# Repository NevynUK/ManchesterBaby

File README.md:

# ManchesterBaby
Manchester Baby (Small Scale Experimental Machine)

The [Manchester Small Scale Experimental Machine](https://en.wikipedia.org/wiki/Manchester_Small-Scale_Experimental_Machine) was the worlds first computer capable of executing a stored program.  The 32-bit architecture utilised an instruction set using only 3 bits allowing 8 possible instructions.  The program was stored in 32 memory locations (or store lines) with both data and program sharing storage (von Neumann architecture).

## Emulator

The Emulator implements a simplified version of the Manchester Baby.  The main program is able to read simple assembler files and execute the programs contained.  The program displays the status of the machine at the start and end of the program run.

Source files for the emulator are available for the following platforms:

* C++ Desktop
* C++ Running on NuttX RTOS (Coming Soon)
* Python Desktop

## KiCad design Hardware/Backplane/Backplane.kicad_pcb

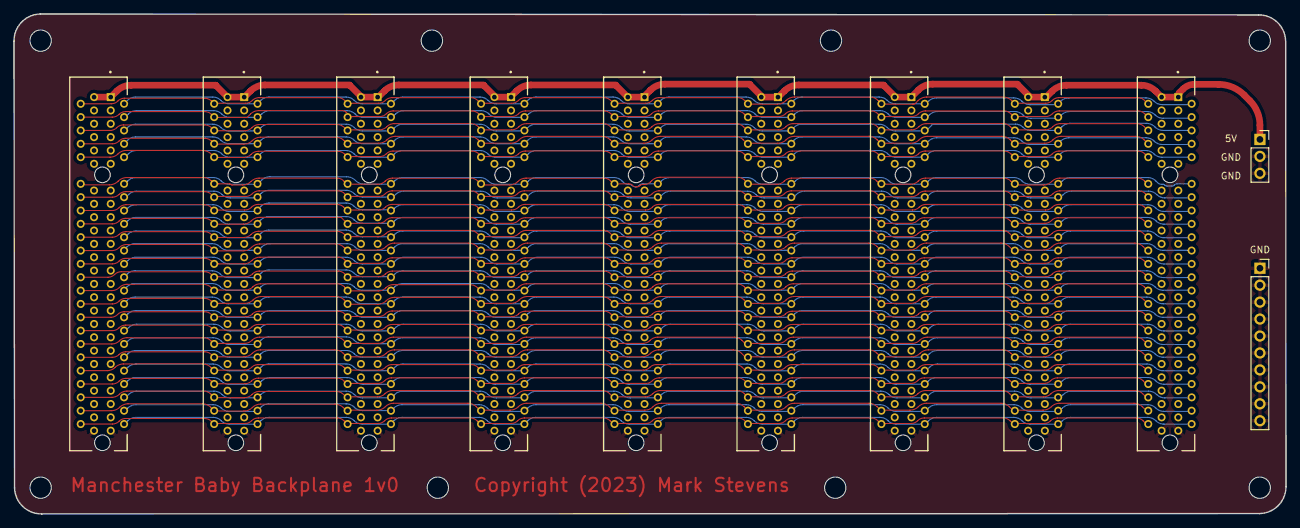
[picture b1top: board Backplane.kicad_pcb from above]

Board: 4 copper layers, 190.6 x 74.9 mm, 19 parts (0 on the bottom side), 96 nets.

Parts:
GND: Conn_01x10; PinSocket_1x10_P2.54mm_Vertical
H1, H2, H3, H4, H5, H6, H7, H8: MountingHole; MountingHole_3.2mm_M3
J1, J2, J3, J5, J6, J7, J8, J9, J10: PCIE-098-02-X-D-TH; SAMTEC_PCIE-098-02-X-D-TH
Power: Conn_01x03; PinSocket_1x03_P2.54mm_Vertical

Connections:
/A2: J1.A2, J2.A2, J3.A2, J5.A2, J6.A2, J7.A2, J8.A2, J9.A2, J10.A2
/A3: J1.A3, J2.A3, J3.A3, J5.A3, J6.A3, J7.A3, J8.A3, J9.A3, J10.A3
/A4: J1.A4, J2.A4, J3.A4, J5.A4, J6.A4, J7.A4, J8.A4, J9.A4, J10.A4
/A5: J1.A5, J2.A5, J3.A5, J5.A5, J6.A5, J7.A5, J8.A5, J9.A5, J10.A5
/A6: J1.A6, J2.A6, J3.A6, J5.A6, J6.A6, J7.A6, J8.A6, J9.A6, J10.A6
/A7: J1.A7, J2.A7, J3.A7, J5.A7, J6.A7, J7.A7, J8.A7, J9.A7, J10.A7
/A8: J1.A8, J2.A8, J3.A8, J5.A8, J6.A8, J7.A8, J8.A8, J9.A8, J10.A8
/A9: J1.A9, J2.A9, J3.A9, J5.A9, J6.A9, J7.A9, J8.A9, J9.A9, J10.A9
/A10: J1.A10, J2.A10, J3.A10, J5.A10, J6.A10, J7.A10, J8.A10, J9.A10, J10.A10
/A11: J1.A11, J2.A11, J3.A11, J5.A11, J6.A11, J7.A11, J8.A11, J9.A11, J10.A11
/A12: J1.A12, J2.A12, J3.A12, J5.A12, J6.A12, J7.A12, J8.A12, J9.A12, J10.A12
/A13: J1.A13, J2.A13, J3.A13, J5.A13, J6.A13, J7.A13, J8.A13, J9.A13, J10.A13
/A14: J1.A14, J2.A14, J3.A14, J5.A14, J6.A14, J7.A14, J8.A14, J9.A14, J10.A14
/A15: J1.A15, J2.A15, J3.A15, J5.A15, J6.A15, J7.A15, J8.A15, J9.A15, J10.A15
/A16: J1.A16, J2.A16, J3.A16, J5.A16, J6.A16, J7.A16, J8.A16, J9.A16, J10.A16
/A17: J1.A17, J2.A17, J3.A17, J5.A17, J6.A17, J7.A17, J8.A17, J9.A17, J10.A17
/A18: J1.A18, J2.A18, J3.A18, J5.A18, J6.A18, J7.A18, J8.A18, J9.A18, J10.A18
/A19: J1.A19, J2.A19, J3.A19, J5.A19, J6.A19, J7.A19, J8.A19, J9.A19, J10.A19
/A20: J1.A20, J2.A20, J3.A20, J5.A20, J6.A20, J7.A20, J8.A20, J9.A20, J10.A20
/A21: J1.A21, J2.A21, J3.A21, J5.A21, J6.A21, J7.A21, J8.A21, J9.A21, J10.A21
/A22: J1.A22, J2.A22, J3.A22, J5.A22, J6.A22, J7.A22, J8.A22, J9.A22, J10.A22
/A23: J1.A23, J2.A23, J3.A23, J5.A23, J6.A23, J7.A23, J8.A23, J9.A23, J10.A23
/A24: J1.A24, J2.A24, J3.A24, J5.A24, J6.A24, J7.A24, J8.A24, J9.A24, J10.A24
/A25: J1.A25, J2.A25, J3.A25, J5.A25, J6.A25, J7.A25, J8.A25, J9.A25, J10.A25
/A26: J1.A26, J2.A26, J3.A26, J5.A26, J6.A26, J7.A26, J8.A26, J9.A26, J10.A26
/A27: J1.A27, J2.A27, J3.A27, J5.A27, J6.A27, J7.A27, J8.A27, J9.A27, J10.A27
/A28: J1.A28, J2.A28, J3.A28, J5.A28, J6.A28, J7.A28, J8.A28, J9.A28, J10.A28
/A29: J1.A29, J2.A29, J3.A29, J5.A29, J6.A29, J7.A29, J8.A29, J9.A29, J10.A29
/A30: J1.A30, J2.A30, J3.A30, J5.A30, J6.A30, J7.A30, J8.A30, J9.A30, J10.A30
/A31: J1.A31, J2.A31, J3.A31, J5.A31, J6.A31, J7.A31, J8.A31, J9.A31, J10.A31
/A32: J1.A32, J2.A32, J3.A32, J5.A32, J6.A32, J7.A32, J8.A32, J9.A32, J10.A32
/A33: J1.A33, J2.A33, J3.A33, J5.A33, J6.A33, J7.A33, J8.A33, J9.A33, J10.A33
/A34: J1.A34, J2.A34, J3.A34, J5.A34, J6.A34, J7.A34, J8.A34, J9.A34, J10.A34
/A35: J1.A35, J2.A35, J3.A35, J5.A35, J6.A35, J7.A35, J8.A35, J9.A35, J10.A35
/A36: J1.A36, J2.A36, J3.A36, J5.A36, J6.A36, J7.A36, J8.A36, J9.A36, J10.A36
/A37: J1.A37, J2.A37, J3.A37, J5.A37, J6.A37, J7.A37, J8.A37, J9.A37, J10.A37
/A38: J1.A38, J2.A38, J3.A38, J5.A38, J6.A38, J7.A38, J8.A38, J9.A38, J10.A38
/A39: J1.A39, J2.A39, J3.A39, J5.A39, J6.A39, J7.A39, J8.A39, J9.A39, J10.A39
/A40: J1.A40, J2.A40, J3.A40, J5.A40, J6.A40, J7.A40, J8.A40, J9.A40, J10.A40
/A41: J1.A41, J2.A41, J3.A41, J5.A41, J6.A41, J7.A41, J8.A41, J9.A41, J10.A41
/A42: J1.A42, J2.A42, J3.A42, J5.A42, J6.A42, J7.A42, J8.A42, J9.A42, J10.A42
/A43: J1.A43, J2.A43, J3.A43, J5.A43, J6.A43, J7.A43, J8.A43, J9.A43, J10.A43
/A44: J1.A44, J2.A44, J3.A44, J5.A44, J6.A44, J7.A44, J8.A44, J9.A44, J10.A44
/A45: J1.A45, J2.A45, J3.A45, J5.A45, J6.A45, J7.A45, J8.A45, J9.A45, J10.A45
/A46: J1.A46, J2.A46, J3.A46, J5.A46, J6.A46, J7.A46, J8.A46, J9.A46, J10.A46
/A47: J1.A47, J2.A47, J3.A47, J5.A47, J6.A47, J7.A47, J8.A47, J9.A47, J10.A47
/A48: J1.A48, J2.A48, J3.A48, J5.A48, J6.A48, J7.A48, J8.A48, J9.A48, J10.A48
/B2: J1.B2, J2.B2, J3.B2, J5.B2, J6.B2, J7.B2, J8.B2, J9.B2, J10.B2
/B3: J1.B3, J2.B3, J3.B3, J5.B3, J6.B3, J7.B3, J8.B3, J9.B3, J10.B3
/B4: J1.B4, J2.B4, J3.B4, J5.B4, J6.B4, J7.B4, J8.B4, J9.B4, J10.B4
/B5: J1.B5, J2.B5, J3.B5, J5.B5, J6.B5, J7.B5, J8.B5, J9.B5, J10.B5
/B6: J1.B6, J2.B6, J3.B6, J5.B6, J6.B6, J7.B6, J8.B6, J9.B6, J10.B6
/B7: J1.B7, J2.B7, J3.B7, J5.B7, J6.B7, J7.B7, J8.B7, J9.B7, J10.B7
/B8: J1.B8, J2.B8, J3.B8, J5.B8, J6.B8, J7.B8, J8.B8, J9.B8, J10.B8
/B9: J1.B9, J2.B9, J3.B9, J5.B9, J6.B9, J7.B9, J8.B9, J9.B9, J10.B9
/B10: J1.B10, J2.B10, J3.B10, J5.B10, J6.B10, J7.B10, J8.B10, J9.B10, J10.B10
/B11: J1.B11, J2.B11, J3.B11, J5.B11, J6.B11, J7.B11, J8.B11, J9.B11, J10.B11
/B12: J1.B12, J2.B12, J3.B12, J5.B12, J6.B12, J7.B12, J8.B12, J9.B12, J10.B12
/B13: J1.B13, J2.B13, J3.B13, J5.B13, J6.B13, J7.B13, J8.B13, J9.B13, J10.B13
/B14: J1.B14, J2.B14, J3.B14, J5.B14, J6.B14, J7.B14, J8.B14, J9.B14, J10.B14
/B15: J1.B15, J2.B15, J3.B15, J5.B15, J6.B15, J7.B15, J8.B15, J9.B15, J10.B15
/B16: J1.B16, J2.B16, J3.B16, J5.B16, J6.B16, J7.B16, J8.B16, J9.B16, J10.B16
/B17: J1.B17, J2.B17, J3.B17, J5.B17, J6.B17, J7.B17, J8.B17, J9.B17, J10.B17
/B18: J1.B18, J2.B18, J3.B18, J5.B18, J6.B18, J7.B18, J8.B18, J9.B18, J10.B18
/B19: J1.B19, J2.B19, J3.B19, J5.B19, J6.B19, J7.B19, J8.B19, J9.B19, J10.B19
/B20: J1.B20, J2.B20, J3.B20, J5.B20, J6.B20, J7.B20, J8.B20, J9.B20, J10.B20
/B21: J1.B21, J2.B21, J3.B21, J5.B21, J6.B21, J7.B21, J8.B21, J9.B21, J10.B21
/B22: J1.B22, J2.B22, J3.B22, J5.B22, J6.B22, J7.B22, J8.B22, J9.B22, J10.B22
/B23: J1.B23, J2.B23, J3.B23, J5.B23, J6.B23, J7.B23, J8.B23, J9.B23, J10.B23
/B24: J1.B24, J2.B24, J3.B24, J5.B24, J6.B24, J7.B24, J8.B24, J9.B24, J10.B24
/B25: J1.B25, J2.B25, J3.B25, J5.B25, J6.B25, J7.B25, J8.B25, J9.B25, J10.B25
/B26: J1.B26, J2.B26, J3.B26, J5.B26, J6.B26, J7.B26, J8.B26, J9.B26, J10.B26
/B27: J1.B27, J2.B27, J3.B27, J5.B27, J6.B27, J7.B27, J8.B27, J9.B27, J10.B27
/B28: J1.B28, J2.B28, J3.B28, J5.B28, J6.B28, J7.B28, J8.B28, J9.B28, J10.B28
/B29: J1.B29, J2.B29, J3.B29, J5.B29, J6.B29, J7.B29, J8.B29, J9.B29, J10.B29
/B30: J1.B30, J2.B30, J3.B30, J5.B30, J6.B30, J7.B30, J8.B30, J9.B30, J10.B30
/B31: J1.B31, J2.B31, J3.B31, J5.B31, J6.B31, J7.B31, J8.B31, J9.B31, J10.B31
/B32: J1.B32, J2.B32, J3.B32, J5.B32, J6.B32, J7.B32, J8.B32, J9.B32, J10.B32
/B33: J1.B33, J2.B33, J3.B33, J5.B33, J6.B33, J7.B33, J8.B33, J9.B33, J10.B33
/B34: J1.B34, J2.B34, J3.B34, J5.B34, J6.B34, J7.B34, J8.B34, J9.B34, J10.B34
/B35: J1.B35, J2.B35, J3.B35, J5.B35, J6.B35, J7.B35, J8.B35, J9.B35, J10.B35
/B36: J1.B36, J2.B36, J3.B36, J5.B36, J6.B36, J7.B36, J8.B36, J9.B36, J10.B36
/B37: J1.B37, J2.B37, J3.B37, J5.B37, J6.B37, J7.B37, J8.B37, J9.B37, J10.B37
/B38: J1.B38, J2.B38, J3.B38, J5.B38, J6.B38, J7.B38, J8.B38, J9.B38, J10.B38
/B39: J1.B39, J2.B39, J3.B39, J5.B39, J6.B39, J7.B39, J8.B39, J9.B39, J10.B39
/B40: J1.B40, J2.B40, J3.B40, J5.B40, J6.B40, J7.B40, J8.B40, J9.B40, J10.B40
/B41: J1.B41, J2.B41, J3.B41, J5.B41, J6.B41, J7.B41, J8.B41, J9.B41, J10.B41
/B42: J1.B42, J2.B42, J3.B42, J5.B42, J6.B42, J7.B42, J8.B42, J9.B42, J10.B42
/B43: J1.B43, J2.B43, J3.B43, J5.B43, J6.B43, J7.B43, J8.B43, J9.B43, J10.B43
/B44: J1.B44, J2.B44, J3.B44, J5.B44, J6.B44, J7.B44, J8.B44, J9.B44, J10.B44
/B45: J1.B45, J2.B45, J3.B45, J5.B45, J6.B45, J7.B45, J8.B45, J9.B45, J10.B45
/B46: J1.B46, J2.B46, J3.B46, J5.B46, J6.B46, J7.B46, J8.B46, J9.B46, J10.B46
/B47: J1.B47, J2.B47, J3.B47, J5.B47, J6.B47, J7.B47, J8.B47, J9.B47, J10.B47
/B48: J1.B48, J2.B48, J3.B48, J5.B48, J6.B48, J7.B48, J8.B48, J9.B48, J10.B48
GND: GND.1, GND.2, GND.3, GND.4, GND.5, GND.6, GND.7, GND.8, GND.9, GND.10, J1.A49, J1.B49, J2.A49, J2.B49, J3.A49, J3.B49, J5.A49, J5.B49, J6.A49, J6.B49, J7.A49, J7.B49, J8.A49, J8.B49, J9.A49, J10.A49, J10.B49, Power.2, Power.3
VCC: J1.A1, J1.B1, J2.A1, J2.B1, J3.A1, J3.B1, J5.A1, J5.B1, J6.A1, J6.B1, J7.A1, J7.B1, J8.A1, J8.B1, J9.A1, J9.B1, J10.A1, J10.B1, Power.1

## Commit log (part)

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2017-02-11 Console emulation of the Manchester Baby
2017-02-11 Preliminary information about the project.
2019-05-26 Update CPU.py
    was generating `ValueError: Single '}' encountered in format string` error
2021-02-18 Added space in header.
2021-03-21 Corrected spelling error in comment.
2021-03-21 Fixed print statements.
2021-03-27 Refactor to make compatible with CircuitPython 6
2021-03-27 Refactor for CircuitPython 6
2021-03-27 Corrected spelling mistake.
2021-03-27 Added DS_Store to ignored files.
2021-03-27 Abstracted Reset and SingleStep
2021-03-27 Moved RunProgram out of the CPU
2021-03-27 Corrected spelling in a comment.
2021-03-27 Exposed CI, PI, Accumulator and StoreLines as properties.
2021-03-27 Additional comments.
2021-03-27 Removed unused file.
2021-03-31 Refactor to use conventional bit ordering
    * Uses modern 32-bit ordering
    * Abstracted the Instructions into their own class
    * Increased number of tests
    * CPU is now separated from the assembler and user interface
2021-03-31 Removed tests directory
    All tests are now in the source files for the appropriate class.
2021-03-31 Using 'from' to import classes.
2021-04-01 Corrected test case.
2021-04-01 Used from xxx import xxx to clean up code.
2021-04-01 Corrected error check.
2021-04-01 Initial implementation of Display Tube using RGB matrix.
2021-04-01 Initial CircuitPython implementation.
2021-04-03 Fixed bug in range for display tube.
2021-04-03 Added run / stop indicator LED
2021-04-15 Renamed the SSEM source files.
2021-04-15 Clear the display as soon as possible.
2021-04-16 Renamed two files to be under 20 characters long.
2021-04-16 File can be selected through UI
    Implemented a basic file selection through the LCD user interface.
2021-04-19 Completed LED and button defintions in UI.
2021-04-19 Basic UI hardware connected to pins.
2021-04-25 Removed test method.
2021-04-25 Add the ability to process binary numbers
2021-04-25 Added additional relative jump instruction.
2021-04-25 Added additional test applications.
2021-04-25 Added dummy console user interface to allow testing.
2021-04-25 * Moved instruction disassembly into the Instruction class. * Made comments consistent between files. * Converted __ for private variables into _ * Renamed UserInterface to PicoUserInterface * Added 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
2021-04-25 Allow a program to be executed with no UI.
2021-04-25 Added from to import statements.
2021-04-25 Added timing and instruction count output to test.
2023-06-09 Restructured the source code folders
2023-06-09 Adding sources back to Python emulation
2023-06-17 Corrected spelling errors.
2023-06-17 Ignoring C++ object files
2023-06-17 Start of C++ port of Python code.
2023-06-17 Basic store line object and tests added.
2023-06-21 Change to constructor parameter ordering and added stdexcept include.
2023-06-25 Mixing C and C++ for NuttX
2023-06-26 Converted register to int32_t and this now hides the type.
2023-06-26 Added CPU class, tests and incorporated into ssem_main.
2023-06-26 Updated CPU class.
2023-06-26 Added additional check.
2023-06-26 Removed warning.
2023-06-29 Reordered initialisation in constructor.
2023-06-29 Test for CPU class.
2023-07-01 Added unknown instruction
2023-07-01 Tidied up compiler warning
2023-07-02 Added support for Binary and reversing bits for UI.
2023-07-02 Reorganisation of responsibility and update UI
2023-07-02 Changes to make compatible with Pico (ARM)
2023-07-02 Added comment to explain vector initialisation.
2023-07-03 Renamed some methods.
2023-07-08 Adding sample SSEM source files.
2023-07-08 Working on universal (Desktop and NuttX) build system.
2023-07-08 Reorganised to allow for desktop unit testing.
2023-07-08 NuttX now using common sources where possible.
2023-07-09 Added constants file.
2023-07-09 Renamed file.
2023-07-09 Added -g option
2023-07-09 Fixed incorrect type.
2023-07-09 Typo.
2023-07-09 Added primitive compiler
2023-07-10 Updated test following new "Instruction" mnemonics
2023-07-10 Added new tests.
2023-07-10 Added comments.
2023-07-10 Tidy up.
2023-07-10 Some memory clean up.
2023-07-12 Run valgrind to generate test results.
2023-07-12 Updated following valgrind results.
2023-07-15 Added Dockerfile to enable valgrind on Mac.
2023-07-15 Trimmed the docker image.
2023-07-15 Change container name.
2023-07-15 Changed working directory.
2023-07-15 Add DEFINES variable to compiler commands.
2023-07-15 Define maximum path length.
2023-07-15 Use maximum path length.
2023-07-15 Corrected check for numbers.
2023-07-15 Added ability to store negative numbers.
2023-07-15 Abstracted unit test execution from main.
2023-07-15 Moved unit tests and now executing a real program.
2023-07-15 Minor tidy up.
2023-07-15 Added additional program output.
2023-07-16 Deleted unused file.
2023-07-16 Added comments and changed variable type.
2023-07-16 Corrected file to be used for the main entry point
2023-07-16 Updated comments.
2023-07-16 Added reamme files.
2023-07-16 Updated main readme.
2023-07-16 Added missing file system initialisation.
2023-07-16 Ignoring valgrind output file.
2023-07-16 Tidying up some memory allocations.
2023-07-16 Deleted objects after use.
2023-07-16 Register file system.
2023-07-16 Register the file system.
2025-11-12 Added datasheets.
2025-11-12 Added Backplane schematic
2025-11-12 Added BOM spreadsheet
2025-11-12 Added copy of the SNP to Verilog translator.
2025-11-12 Added System Verilog implmentation.
2025-11-12 Added readme for the HDL code.

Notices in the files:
Hardware/Backplane/Backplane.kicad_pcb:
Copyright (2023) Mark Stevens
